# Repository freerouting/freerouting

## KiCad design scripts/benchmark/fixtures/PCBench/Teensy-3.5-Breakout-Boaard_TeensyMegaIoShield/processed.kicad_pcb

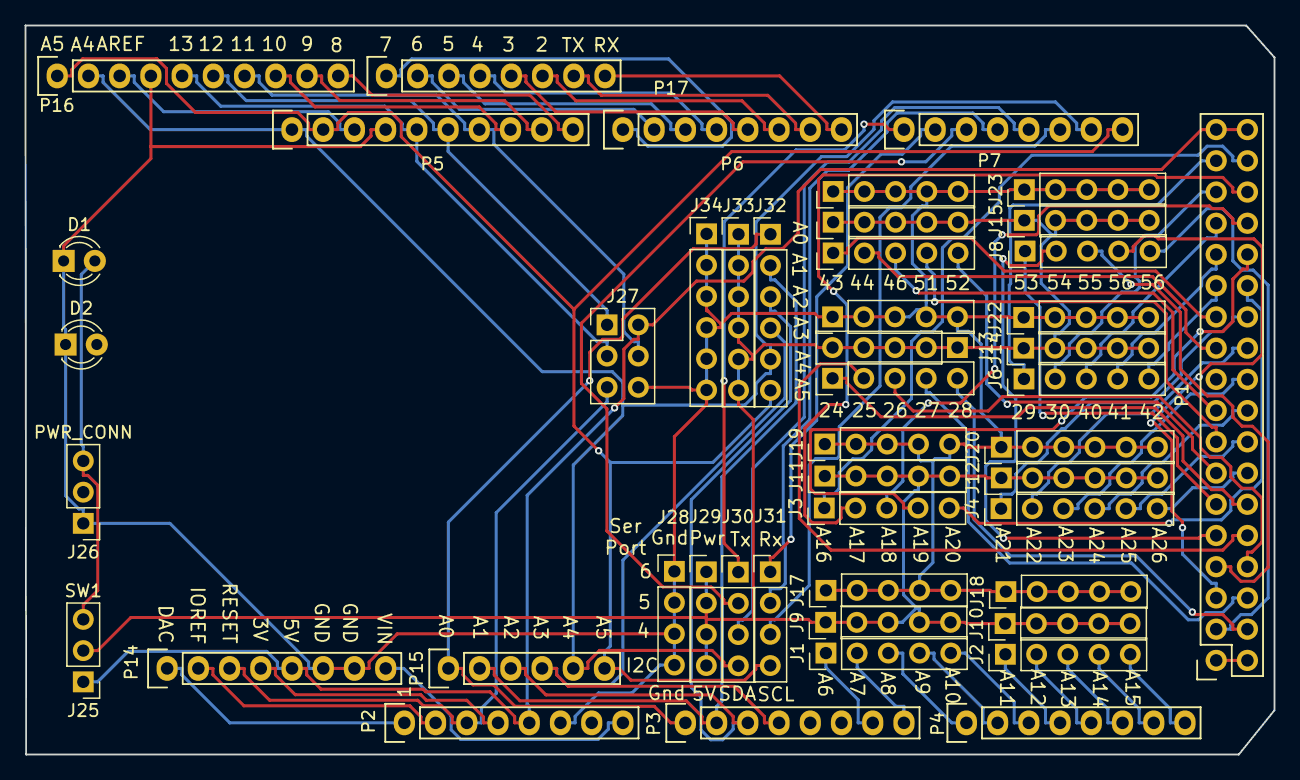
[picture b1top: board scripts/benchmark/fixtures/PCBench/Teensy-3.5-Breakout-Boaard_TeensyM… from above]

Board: 2 copper layers, 101.6 x 59.3 mm, 47 parts (0 on the bottom side), 78 nets.

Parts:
D1: RLED; LED_D3.0mm
D2: YLED; LED_D3.0mm
J1, J2, J3, J5, J6, J7, J8, J9, J10, J11, J13, J14, J15, J16, J17, J18, J19, J21, J22, J23, J24: CONN_01X05; Pin_Header_Straight_1x05_Pitch2.54mm
J4, J12, J20, J32, J33, J34: CONN_01X06; Pin_Header_Straight_1x06_Pitch2.54mm
J25: SW1; Pin_Header_Straight_1x03_Pitch2.54mm
J26: PWR_CONN; Pin_Header_Straight_1x03_Pitch2.54mm
J27: CONN_02X03; Pin_Header_Straight_2x03_Pitch2.54mm
J28, J29, J30, J31: CONN_01X04; Pin_Header_Straight_1x04_Pitch2.54mm
P1: Digital; Socket_Strip_Arduino_2x18
P2, P14: Power; Socket_Strip_Arduino_1x08
P3, P4: Analog; Socket_Strip_Arduino_1x08
P5: PWM; Socket_Strip_Arduino_1x10
P6: PWM; Socket_Strip_Arduino_1x08
P7: Communication; Socket_Strip_Arduino_1x08
P15: Analog; Socket_Strip_Arduino_1x06
P16: Digital; Socket_Strip_Arduino_1x10
P17: Digital; Socket_Strip_Arduino_1x08

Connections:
+3V3: P2.4, P14.4
+5V: J25.1, J27.2, P1.35, P1.36, P2.5, P14.5
/0(Rx0): P6.8, P17.8
/1(Tx0): P6.7, P17.7
/2(**): P6.6, P17.6
/3(**): P6.5, P17.5
/4(**): P6.4, P17.4
/5(**): P6.3, P17.3
/6(**): P6.2, P17.2
/7(**): P6.1, P17.1
/8(**): P5.10, P16.10
/9(**): P5.9, P16.9
/10(**/SS): P5.8, P16.8
/11(**/MOSI): J27.4, P5.7, P16.7
/12(MISO): J27.1, P5.6, P16.6
/13(SCK): J27.3, P5.5, P16.5
/24: J5.1, P1.12
/25: J5.2, P1.10
/26: J5.3, P1.8
/27: J5.4, P1.6
/28: J5.5, P1.4
/29: J6.1, P1.33
/30: J6.2, P1.31
/40: J6.3, P1.29
/41: J6.4, P1.27
/42: J6.5, P1.25
/43: J7.1, P1.23
/44: J7.2, P1.21
/46: J7.3, P1.17
/47(RX6): J31.1, P7.2
/48(TX6): J30.1, P7.1
/51: J7.4, P1.15
/52: J7.5, P1.13
/53: J8.1, P1.11
/54: J8.2, P1.9
/55: J8.3, P1.7
/56: J8.4, P1.5
/57: J8.5, P1.3
/A0: J32.1, P3.1, P15.1
/A1: J32.2, P3.2, P15.2
/A2: J32.3, P3.3, P15.3
/A3: J32.4, P3.4, P15.4
/A4(SDA): J30.4, J32.5, P5.1, P7.7, P15.5, P16.2
/A5(SCL): J31.4, J32.6, P5.2, P7.8, P15.6, P16.1
/A6: J1.1, P3.7
/A7: J1.2, P3.8
/A8: J1.3, P4.1
/A9: J1.4, P4.2
/A10: J1.5, P4.3
/A11: J2.1, P4.4
/A12: J2.2, P4.5
/A12(RX4): J31.3, P7.6
/A13: J2.3, P4.6
/A13(TX4): J30.3, P7.5
/A14: J2.4, P4.7
/A14(TX5): J30.2, P7.3
/A15: J2.5, P4.8
/A15(RX5): J31.2, P7.4
/A16: J3.1, P1.34
/A17: J3.2, P1.32
/A18: J3.3, P1.30
/A19: J3.4, P1.28
/A20: J3.5, P1.26
/A21: J4.1, P1.24
/A22: J4.2, P1.22
/A23: J4.3, P1.20
/A24: J4.4, P1.18
/A25: J4.5, P1.16
/A26: J4.6, P1.14
/AREF: P5.3, P16.3
/IOREF: P2.2, P14.2
/Reset: J27.5, P2.3, P14.3
/Vin: P2.8, P14.8
GND: D1.1, D2.1, J17.1, J17.2, J17.3, J17.4, J17.5, J18.1, J18.2, J18.3, J18.4, J18.5, J19.1, J19.2, J19.3, J19.4, J19.5, J20.1, J20.2, J20.3, J20.4, J20.5, J20.6, J21.1, J21.2, J21.3, J21.4, J21.5, J22.1, J22.2, J22.3, J22.4, J22.5, J23.1, J23.2, J23.3, J23.4, J23.5, J24.1, J24.2, J24.3, J24.4, J24.5, J26.1, J27.6, J28.1, J28.2, J28.3, J28.4, J34.1, J34.2, J34.3, J34.4, J34.5, J34.6, P2.6, P5.4, P14.6, P14.7, P16.4
unnamed: D1.2, J25.3, J26.3
unnamed: J9.1, J9.2, J9.3, J9.4, J9.5, J10.1, J10.2, J10.3, J10.4, J10.5, J11.1, J11.2, J11.3, J11.4, J11.5, J12.1, J12.2, J12.3, J12.4, J12.5, J12.6, J13.1, J13.2, J13.3, J13.4, J13.5, J14.1, J14.2, J14.3, J14.4, J14.5, J15.1, J15.2, J15.3, J15.4, J15.5, J16.1, J16.2, J16.3, J16.4, J16.5, J25.2, J29.1, J29.2, J29.3, J29.4, J33.1, J33.2, J33.3, J33.4, J33.5, J33.6
unnamed: P1.1, P1.2
unnamed: P2.1, P14.1

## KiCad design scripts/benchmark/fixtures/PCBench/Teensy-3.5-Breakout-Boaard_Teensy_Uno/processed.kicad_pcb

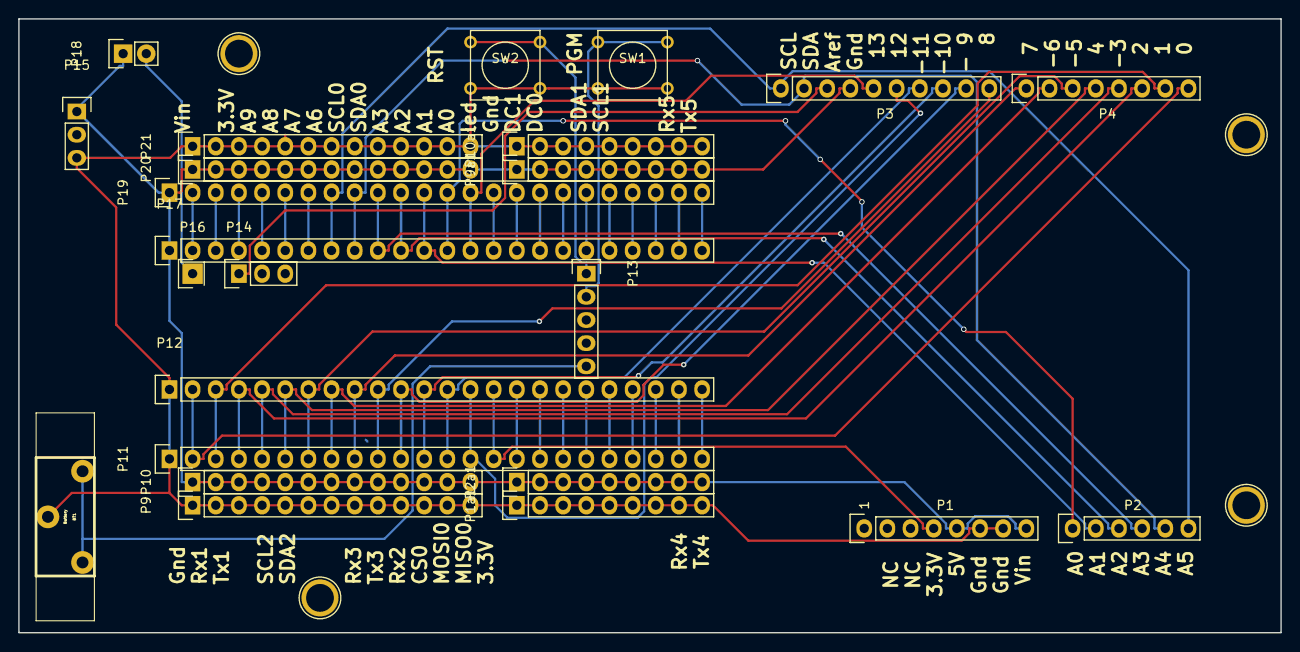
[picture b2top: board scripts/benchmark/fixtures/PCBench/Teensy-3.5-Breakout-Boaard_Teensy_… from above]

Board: 2 copper layers, 138.4 x 67.3 mm, 28 parts (0 on the bottom side), 53 nets.

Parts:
BT1: Battery; BAT_HOLDER_2032
P1: Power; Socket_Strip_Arduino_1x08
P1a1, P2a1, P9a1: CONN_01X09; Pin_Header_Straight_1x09
P2: Analog; Socket_Strip_Arduino_1x06
P3: Digital; Socket_Strip_Arduino_1x10
P4: Digital; Socket_Strip_Arduino_1x08
P5, P6, P7, P8: CONN_01X01; Arduino_1pin
P9, P10, P20, P21: CONN_01X13; Pin_Header_Straight_1x13
P10a1: CONN_01X10; Pin_Header_Straight_1x09
P11, P19: CONN_01X24; Pin_Header_Straight_1x24
P12, P17: CONN_01X24; Socket_Strip_Straight_1x24
P13: CONN_01X05; Socket_Strip_Straight_1x05
P14: CONN_01X03; Socket_Strip_Straight_1x03
P15: CONN_01X03; Pin_Header_Straight_1x03
P16: CONN_01X01; Socket_Strip_Straight_1x01
P18: CONN_01X02; Pin_Header_Straight_1x02
SW1, SW2: SW_PUSH_SMALL_H; SW_PUSH_SMALL

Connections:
/0(Rx): P4.8, P11.2, P12.2
/1(Tx): P4.7, P11.3, P12.3
/3(**): P4.5, P11.5, P12.5
/4: P4.4, P11.6, P12.6
/5(**): P4.3, P11.7, P12.7
/6(**): P4.2, P11.8, P12.8
/9(**): P3.9, P11.11, P12.11
/10(**/SS): P3.8, P11.12, P12.12
/11(**/MOSI): P3.7, P11.13, P12.13
/12(MISO): P3.6, P11.14, P12.14
/13(SCK): P3.5, P17.14, P19.14
/A0: P2.1, P17.13, P19.13
/A1: P2.2, P17.12, P19.12
/A2: P2.3, P17.11, P19.11
/A3: P2.4, P17.10, P19.10
/A5(SCL): P2.6, P3.1, P17.8, P19.8
unnamed: BT1.1, P13.5
unnamed: BT1.2, P1.6, P1.7, P1a1.1, P1a1.2, P1a1.3, P1a1.4, P1a1.5, P1a1.6, P1a1.7, P1a1.8, P1a1.9, P9.1, P9.2, P9.3, P9.4, P9.5, P9.6, P9.7, P9.8, P9.9, P9.10, P9.11, P9.12, P9.13, P10a1.1, P10a1.2, P10a1.3, P10a1.4, P10a1.5, P10a1.6, P10a1.7, P10a1.8, P10a1.9, P11.1, P12.1, P15.3, P21.1, P21.2, P21.3, P21.4, P21.5, P21.6, P21.7, P21.8, P21.9, P21.10, P21.11, P21.12, P21.13, SW1.2, SW2.2
unnamed: P1.4, P11.15
unnamed: P1.5, P1.8, P2a1.1, P2a1.2, P2a1.3, P2a1.4, P2a1.5, P2a1.6, P2a1.7, P2a1.8, P2a1.9, P3.4, P9a1.1, P9a1.2, P9a1.3, P9a1.4, P9a1.5, P9a1.6, P9a1.7, P9a1.8, P9a1.9, P10.1, P10.2, P10.3, P10.4, P10.5, P10.6, P10.7, P10.8, P10.9, P10.10, P10.11, P10.12, P10.13, P15.1, P17.1, P18.1, P19.1, P20.1, P20.2, P20.3, P20.4, P20.5, P20.6, P20.7, P20.8, P20.9, P20.10, P20.11, P20.12, P20.13
unnamed: P4.6, P11.4, P12.4
unnamed: P4.1, P11.9, P12.9
unnamed: P3.10, P11.10, P12.10
unnamed: P11.16, P12.16
unnamed: P11.17, P12.17
unnamed: P11.18, P12.18
unnamed: P11.19, P12.19
unnamed: P11.20, P12.20
unnamed: P11.21, P12.21
unnamed: P11.22, P12.22
unnamed: P11.23, P12.23
unnamed: P11.24, P12.24
unnamed: P13.1, SW2.1
unnamed: P13.2, SW1.1
unnamed: P3.3, P14.1
unnamed: P16.1, P18.2
unnamed: P17.2, P19.2
unnamed: P17.3, P19.3
unnamed: P17.4, P19.4
unnamed: P17.5, P19.5
unnamed: P17.6, P19.6
unnamed: P17.7, P19.7
unnamed: P2.5, P3.2, P17.9, P19.9
unnamed: P17.15, P19.15
unnamed: P17.16, P19.16
unnamed: P17.17, P19.17
unnamed: P17.18, P19.18
unnamed: P17.19, P19.19
unnamed: P17.20, P19.20
unnamed: P17.21, P19.21
unnamed: P17.22, P19.22
unnamed: P17.23, P19.23
unnamed: P17.24, P19.24

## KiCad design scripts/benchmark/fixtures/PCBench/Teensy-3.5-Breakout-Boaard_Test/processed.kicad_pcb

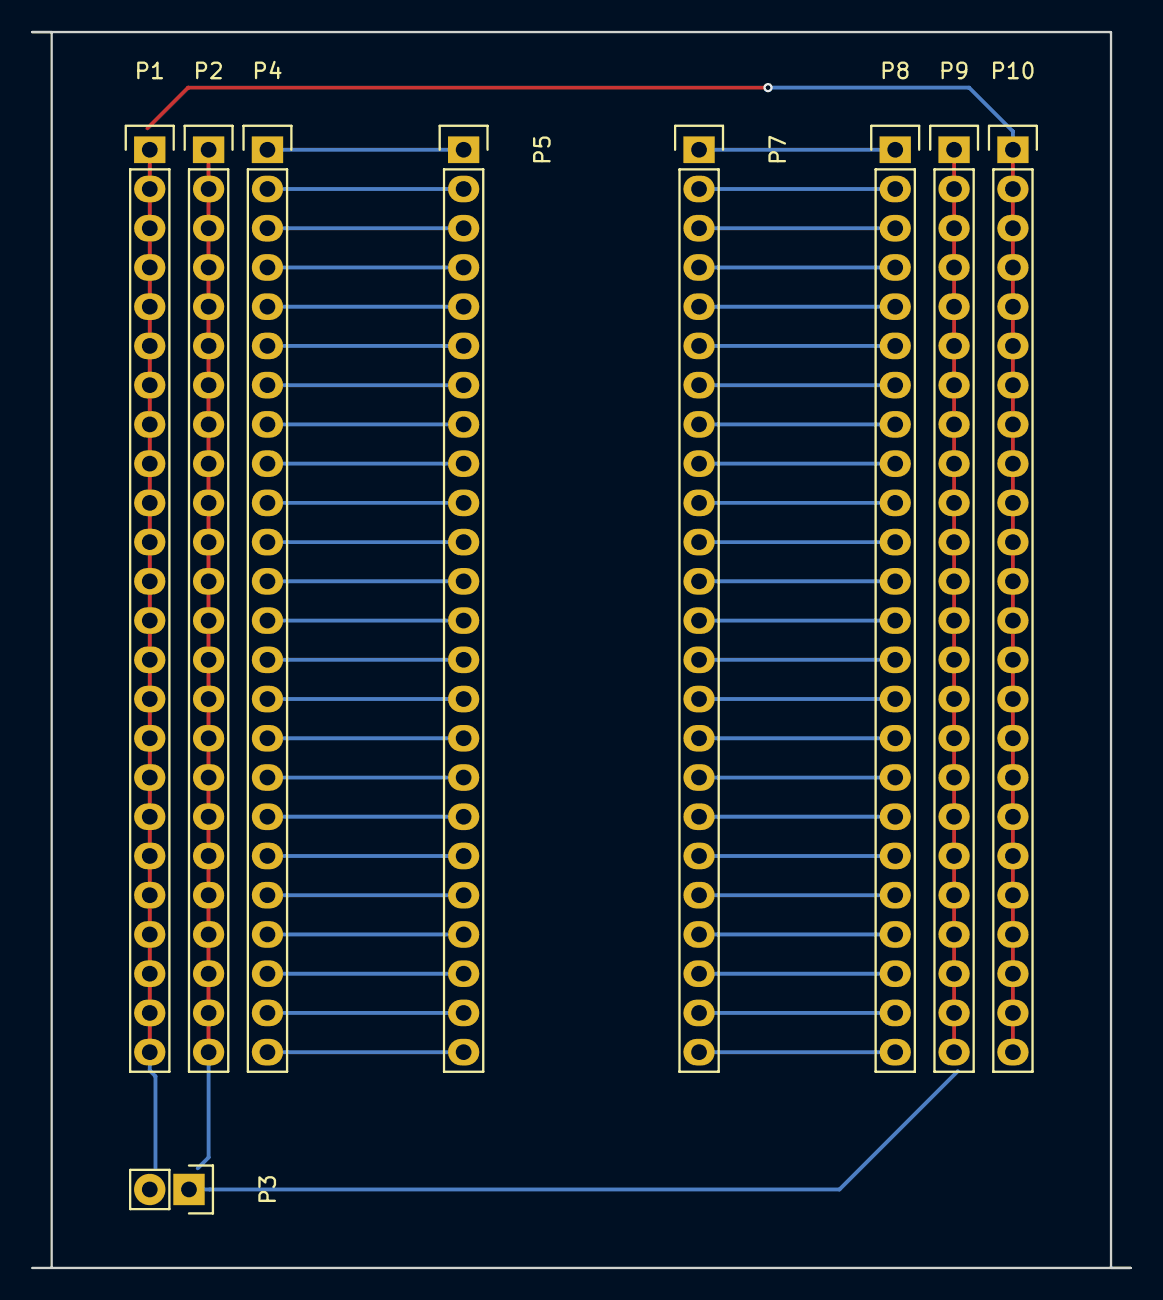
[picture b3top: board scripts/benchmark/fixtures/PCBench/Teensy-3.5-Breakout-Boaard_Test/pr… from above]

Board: 2 copper layers, 71.1 x 80.0 mm, 9 parts (0 on the bottom side), 52 nets.

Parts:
P1, P2, P4, P8, P9, P10: CONN_01X24; Pin_Header_Straight_1x24
P3: CONN_01X02; Pin_Header_Straight_1x02
P5, P7: CONN_01X24; Socket_Strip_Straight_1x24

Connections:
unnamed: P1.1, P1.2, P1.3, P1.4, P1.5, P1.6, P1.7, P1.8, P1.9, P1.10, P1.11, P1.12, P1.13, P1.14, P1.15, P1.16, P1.17, P1.18, P1.19, P1.20, P1.21, P1.22, P1.23, P1.24
unnamed: P2.1, P2.2, P2.3, P2.4, P2.5, P2.6, P2.7, P2.8, P2.9, P2.10, P2.11, P2.12, P2.13, P2.14, P2.15, P2.16, P2.17, P2.18, P2.19, P2.20, P2.21, P2.22, P2.23, P2.24
unnamed: P4.1, P5.1
unnamed: P4.2, P5.2
unnamed: P4.3, P5.3
unnamed: P4.4, P5.4
unnamed: P4.5, P5.5
unnamed: P4.6, P5.6
unnamed: P4.7, P5.7
unnamed: P4.8, P5.8
unnamed: P4.9, P5.9
unnamed: P4.10, P5.10
unnamed: P4.11, P5.11
unnamed: P4.12, P5.12
unnamed: P4.13, P5.13
unnamed: P4.14, P5.14
unnamed: P4.15, P5.15
unnamed: P4.16, P5.16
unnamed: P4.17, P5.17
unnamed: P4.18, P5.18
unnamed: P4.19, P5.19
unnamed: P4.20, P5.20
unnamed: P4.21, P5.21
unnamed: P4.22, P5.22
unnamed: P4.23, P5.23
unnamed: P4.24, P5.24
unnamed: P7.1, P8.1
unnamed: P7.2, P8.2
unnamed: P7.3, P8.3
unnamed: P7.4, P8.4
unnamed: P7.5, P8.5
unnamed: P7.6, P8.6
unnamed: P7.7, P8.7
unnamed: P7.8, P8.8
unnamed: P7.9, P8.9
unnamed: P7.10, P8.10
unnamed: P7.11, P8.11
unnamed: P7.12, P8.12
unnamed: P7.13, P8.13
unnamed: P7.14, P8.14
unnamed: P7.15, P8.15
unnamed: P7.16, P8.16
unnamed: P7.17, P8.17
unnamed: P7.18, P8.18
unnamed: P7.19, P8.19
unnamed: P7.20, P8.20
unnamed: P7.21, P8.21
unnamed: P7.22, P8.22
unnamed: P7.23, P8.23
unnamed: P7.24, P8.24
unnamed: P9.1, P9.2, P9.3, P9.4, P9.5, P9.6, P9.7, P9.8, P9.9, P9.10, P9.11, P9.12, P9.13, P9.14, P9.15, P9.16, P9.17, P9.18, P9.19, P9.20, P9.21, P9.22, P9.23, P9.24
unnamed: P10.1, P10.2, P10.3, P10.4, P10.5, P10.6, P10.7, P10.8, P10.9, P10.10, P10.11, P10.12, P10.13, P10.14, P10.15, P10.16, P10.17, P10.18, P10.19, P10.20, P10.21, P10.22, P10.23, P10.24
